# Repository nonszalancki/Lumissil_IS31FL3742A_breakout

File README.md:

# Breakout board for Lumissil IS31FL3742A LED driver
Simple break out board to add a bit of colours to your project.

## Usage/Example

## How to use it?
I designed these breakout boards with building rgb keyborad in mind. However you can use it in any project that you desire.
1. Download the gerber files.
2. Send them to your supplier of choice.
3. Take a look at iBOM and figure what parts you need.
4. Solder everything and connect to your microcontroller of choice. You can choose i2c address by solder pads on tha back of the breakout board.

5. Enjoy!

## Building
You can use [iBOM](https://nonszalancki.github.io/Lumissil_IS31FL3742A_breakout/) here to help you with component placement.

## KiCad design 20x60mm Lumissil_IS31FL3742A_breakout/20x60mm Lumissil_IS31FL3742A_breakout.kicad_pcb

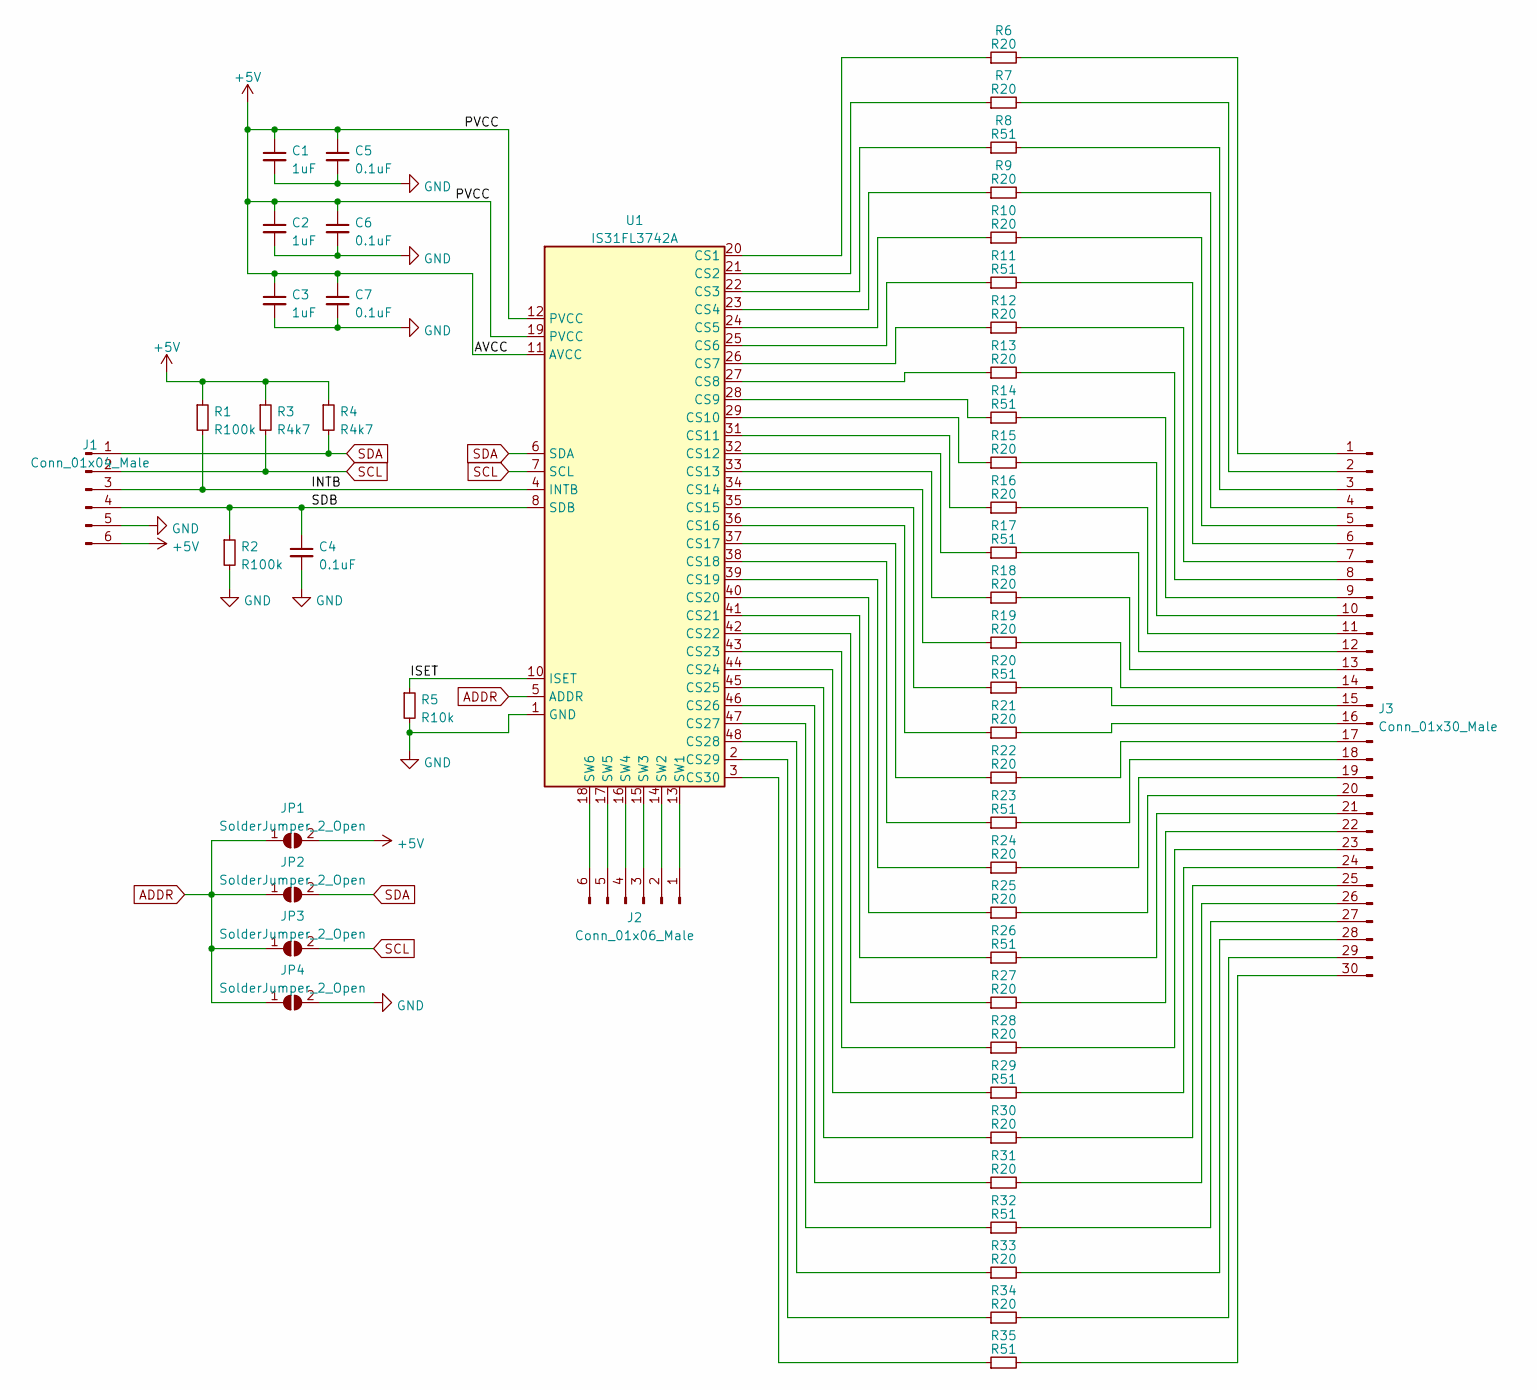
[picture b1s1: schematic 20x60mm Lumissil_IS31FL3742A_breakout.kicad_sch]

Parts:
C1, C2, C3: 1uF; C_0603_1608Metric
C4, C5, C6, C7: 0.1uF; C_0603_1608Metric
J1: Conn_01x04_Male; PinHeader_1x06_P2.00mm_Vertical
J2: Conn_01x06_Male; PinHeader_1x06_P2.00mm_Vertical
J3: Conn_01x30_Male; PinHeader_1x30_P2.00mm_Vertical
JP1, JP2, JP3, JP4: SolderJumper_2_Open; SolderJumper-2_P1.3mm_Open_TrianglePad1.0x1.5mm
R1, R2: R100k; R_0805_2012Metric
R3, R4: R4k7; R_0805_2012Metric
R5: R10k; R_0805_2012Metric
R6, R7, R9, R10, R12, R13, R15, R16, R18, R19, R21, R22, R24, R25, R27, R28, R30, R31, R33, R34: R20; R_0805_2012Metric
R8, R11, R14, R17, R20, R23, R26, R29, R32, R35: R51; R_0805_2012Metric
U1: IS31FL3742A; QFN-48-1EP_6x6mm_P0.4mm_EP4.2x4.2mm_ThermalVias

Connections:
+5V: C1.1, C2.1, C3.1, C5.1, C6.1, C7.1, J1.6, JP1.2 (B), R1.1, R3.1, R4.1, U1.11 (AVCC), U1.12 (PVCC), U1.19 (PVCC); also elsewhere on the board
/ISET: R5.1, U1.10 (ISET)
ADDR: JP1.1 (A), JP2.1 (A), JP3.1 (A), JP4.1 (A), U1.5 (ADDR); also elsewhere on the board
GND: C1.2, C2.2, C3.2, C4.2, C5.2, C6.2, C7.2, J1.5, JP4.2 (B), R2.2, R5.2, U1.1 (GND), U1.9 (GND), U1.30 (GND), U1.49 (GND); also elsewhere on the board
unnamed: J2.1, U1.13 (SW1)
unnamed: J2.2, U1.14 (SW2)
unnamed: J2.3, U1.15 (SW3)
unnamed: J2.4, U1.16 (SW4)
unnamed: J2.5, U1.17 (SW5)
unnamed: J2.6, U1.18 (SW6)
unnamed: J3.1, R6.2
unnamed: J3.2, R7.2
unnamed: J3.3, R8.2
unnamed: J3.4, R9.2
unnamed: J3.5, R10.2
unnamed: J3.6, R11.2
unnamed: J3.7, R12.2
unnamed: J3.8, R13.2
unnamed: J3.9, R14.2
unnamed: J3.10, R15.2
unnamed: J3.11, R16.2
unnamed: J3.12, R17.2
unnamed: J3.13, R18.2
unnamed: J3.14, R19.2
unnamed: J3.15, R20.2
unnamed: J3.16, R21.2
unnamed: J3.17, R22.2
unnamed: J3.18, R23.2
unnamed: J3.19, R24.2
unnamed: J3.20, R25.2
unnamed: J3.21, R26.2
unnamed: J3.22, R27.2
unnamed: J3.23, R28.2
unnamed: J3.24, R29.2
unnamed: J3.25, R30.2
unnamed: J3.26, R31.2
unnamed: J3.27, R32.2
unnamed: J3.28, R33.2
unnamed: J3.29, R34.2
unnamed: J3.30, R35.2
unnamed: R6.1, U1.20 (CS1)
unnamed: R7.1, U1.21 (CS2)
unnamed: R8.1, U1.22 (CS3)
unnamed: R9.1, U1.23 (CS4)
unnamed: R10.1, U1.24 (CS5)
unnamed: R11.1, U1.25 (CS6)
unnamed: R12.1, U1.26 (CS7)
unnamed: R13.1, U1.27 (CS8)
unnamed: R14.1, U1.28 (CS9)
unnamed: R15.1, U1.29 (CS10)
unnamed: R16.1, U1.31 (CS11)
unnamed: R17.1, U1.32 (CS12)
unnamed: R18.1, U1.33 (CS13)
unnamed: R19.1, U1.34 (CS14)
unnamed: R20.1, U1.35 (CS15)
unnamed: R21.1, U1.36 (CS16)
unnamed: R22.1, U1.37 (CS17)
unnamed: R23.1, U1.38 (CS18)
unnamed: R24.1, U1.39 (CS19)
unnamed: R25.1, U1.40 (CS20)
unnamed: R26.1, U1.41 (CS21)
unnamed: R27.1, U1.42 (CS22)
unnamed: R28.1, U1.43 (CS23)
unnamed: R29.1, U1.44 (CS24)
unnamed: R30.1, U1.45 (CS25)
unnamed: R31.1, U1.46 (CS26)
unnamed: R32.1, U1.47 (CS27)
unnamed: R33.1, U1.48 (CS28)
unnamed: R34.1, U1.2 (CS29)
unnamed: R35.1, U1.3 (CS30)
SCL: J1.2, JP3.2 (B), R3.2, U1.7 (SCL); also elsewhere on the board

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
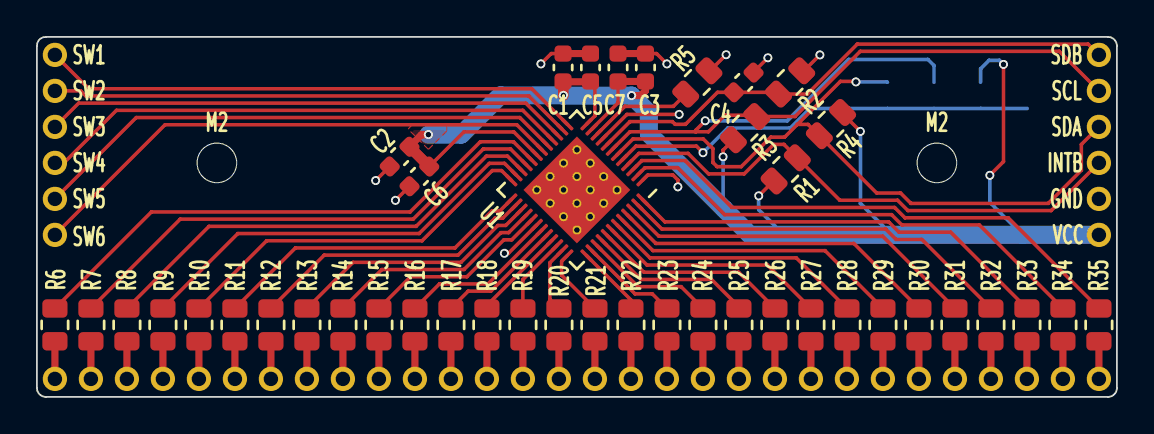
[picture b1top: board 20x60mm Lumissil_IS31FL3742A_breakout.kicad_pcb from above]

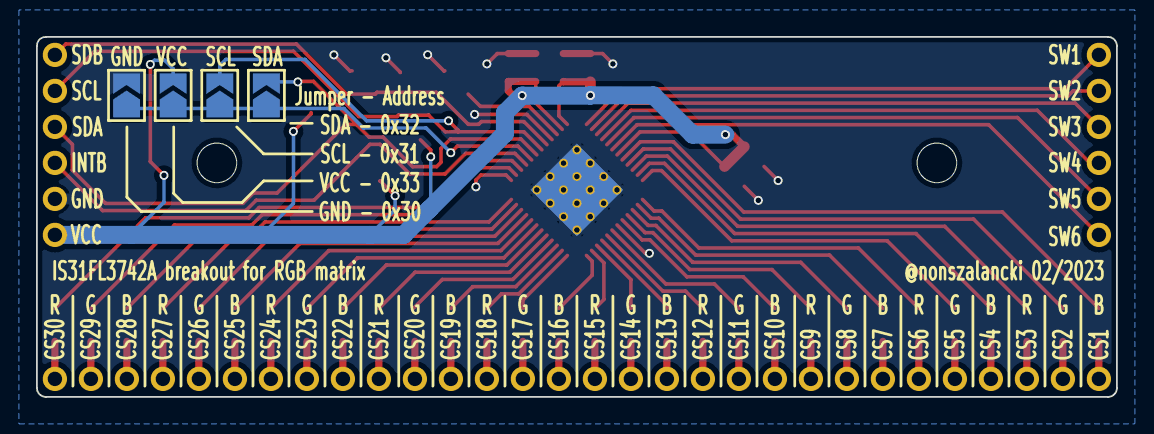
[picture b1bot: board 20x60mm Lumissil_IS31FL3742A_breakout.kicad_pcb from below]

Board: 2 copper layers, 60.0 x 20.0 mm, 52 parts (4 on the bottom side), 74 nets.

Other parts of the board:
GND: SolderJumper_2_Open; SolderJumper-2_P1.3mm_Open_TrianglePad1.0x1.5mm
M2, M2#2: MountingHole_2.2mm_M2_DIN965
SCL: SolderJumper_2_Open; SolderJumper-2_P1.3mm_Open_TrianglePad1.0x1.5mm
SDA: SolderJumper_2_Open; SolderJumper-2_P1.3mm_Open_TrianglePad1.0x1.5mm
VCC: SolderJumper_2_Open; SolderJumper-2_P1.3mm_Open_TrianglePad1.0x1.5mm

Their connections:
+5V: VCC.2 (B); also elsewhere on the board
ADDR: GND.1 (A), SCL.1 (A), SDA.1 (A), VCC.1 (A); also elsewhere on the board
GND: GND.2 (B); also elsewhere on the board
SCL: SCL.2 (B); also elsewhere on the board

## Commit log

2024-05-26 added README and img dir
2024-05-26 Gif change
2024-09-19 minor changes to gitignore, added more img
2024-09-19 added more img
2024-09-19 added ibom to docs
2024-09-19 added solderpads png
